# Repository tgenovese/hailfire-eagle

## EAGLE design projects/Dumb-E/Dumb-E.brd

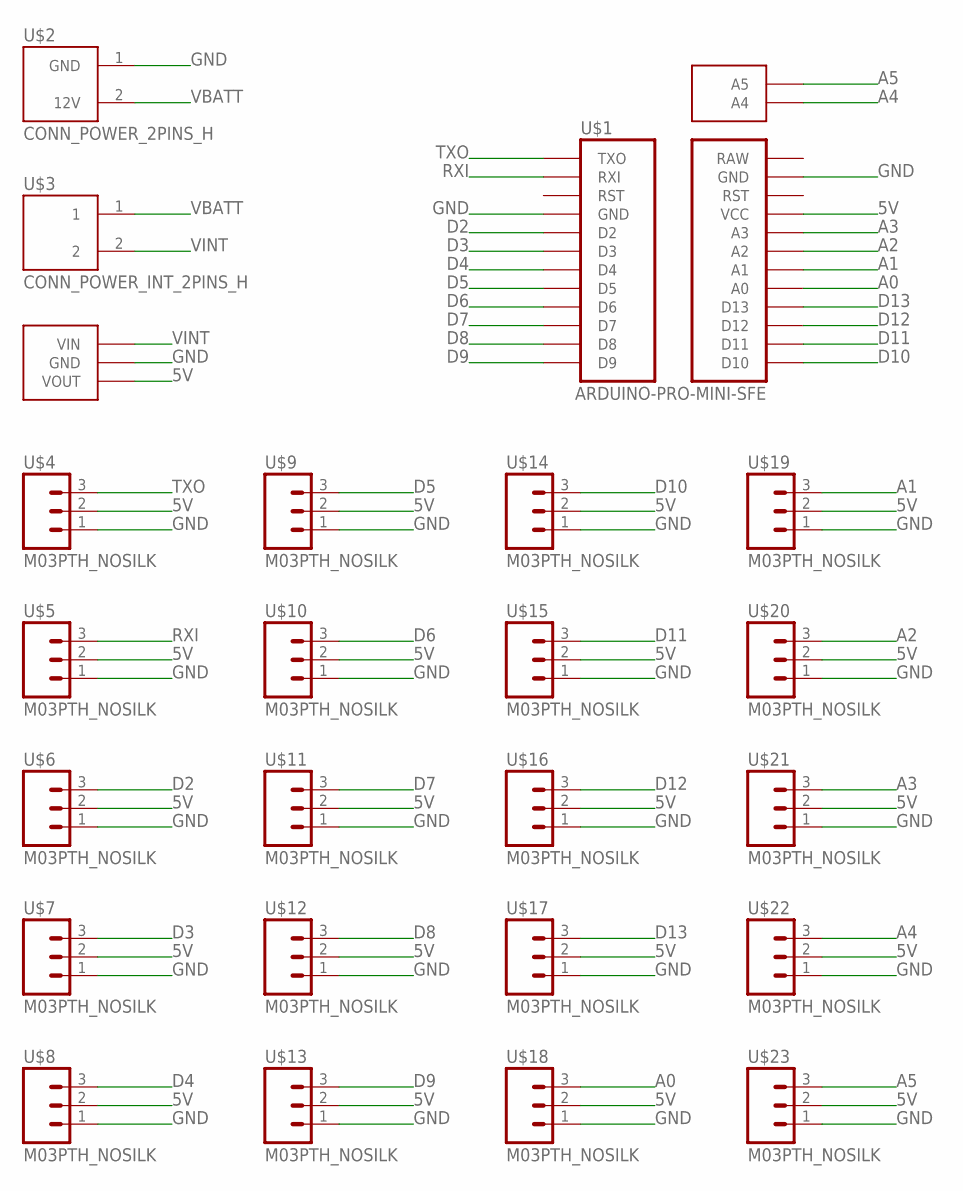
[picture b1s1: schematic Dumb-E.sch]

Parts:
U$1: ARDUINO-PRO-MINI-SFE; ARDUINO-PRO-MINI
U$2: CONN_POWER_2PINS_H; 2PINS_5MM_90DEG
U$3: CONN_POWER_INT_2PINS_H; 2PINS_5MM_90DEG
U$4, U$5, U$6, U$7, U$8, U$9, U$10, U$11, U$12, U$13, U$14, U$15, U$16, U$17, U$18, U$19, U$20, U$21, U$22, U$23: M03PTH_NOSILK; 1X03/NOSILK
U$25: DE-SW0XX

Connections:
5V: U$1.P$17 (VCC), U$4.2, U$5.2, U$6.2, U$7.2, U$8.2, U$9.2, U$10.2, U$11.2, U$12.2, U$13.2, U$14.2, U$15.2, U$16.2, U$17.2, U$18.2, U$19.2, U$20.2, U$21.2, U$22.2, U$23.2, U$25.VOUT
A0: U$1.P$9 (A0), U$18.3
A1: U$1.P$11 (A1), U$19.3
A2: U$1.P$13 (A2), U$20.3
A3: U$1.P$15 (A3), U$21.3
A4: U$1.P$26 (A4), U$22.3
A5: U$1.P$25 (A5), U$23.3
D2: U$1.P$16 (D2), U$6.3
D3: U$1.P$14 (D3), U$7.3
D4: U$1.P$12 (D4), U$8.3
D5: U$1.P$10 (D5), U$9.3
D6: U$1.P$8 (D6), U$10.3
D7: U$1.P$6 (D7), U$11.3
D8: U$1.P$4 (D8), U$12.3
D9: U$1.P$2 (D9), U$13.3
D10: U$1.P$1 (D10), U$14.3
D11: U$1.P$3 (D11), U$15.3
D12: U$1.P$5 (D12), U$16.3
D13: U$1.P$7 (D13), U$17.3
GND: U$1.P$18 (GND), U$1.P$21 (GND), U$2.1 (GND), U$4.1, U$5.1, U$6.1, U$7.1, U$8.1, U$9.1, U$10.1, U$11.1, U$12.1, U$13.1, U$14.1, U$15.1, U$16.1, U$17.1, U$18.1, U$19.1, U$20.1, U$21.1, U$22.1, U$23.1, U$25.GND
RXI: U$1.P$22 (RXI), U$5.3
TXO: U$1.P$24 (TXO), U$4.3
VBATT: U$2.2 (12V), U$3.1
VINT: U$3.2, U$25.VIN

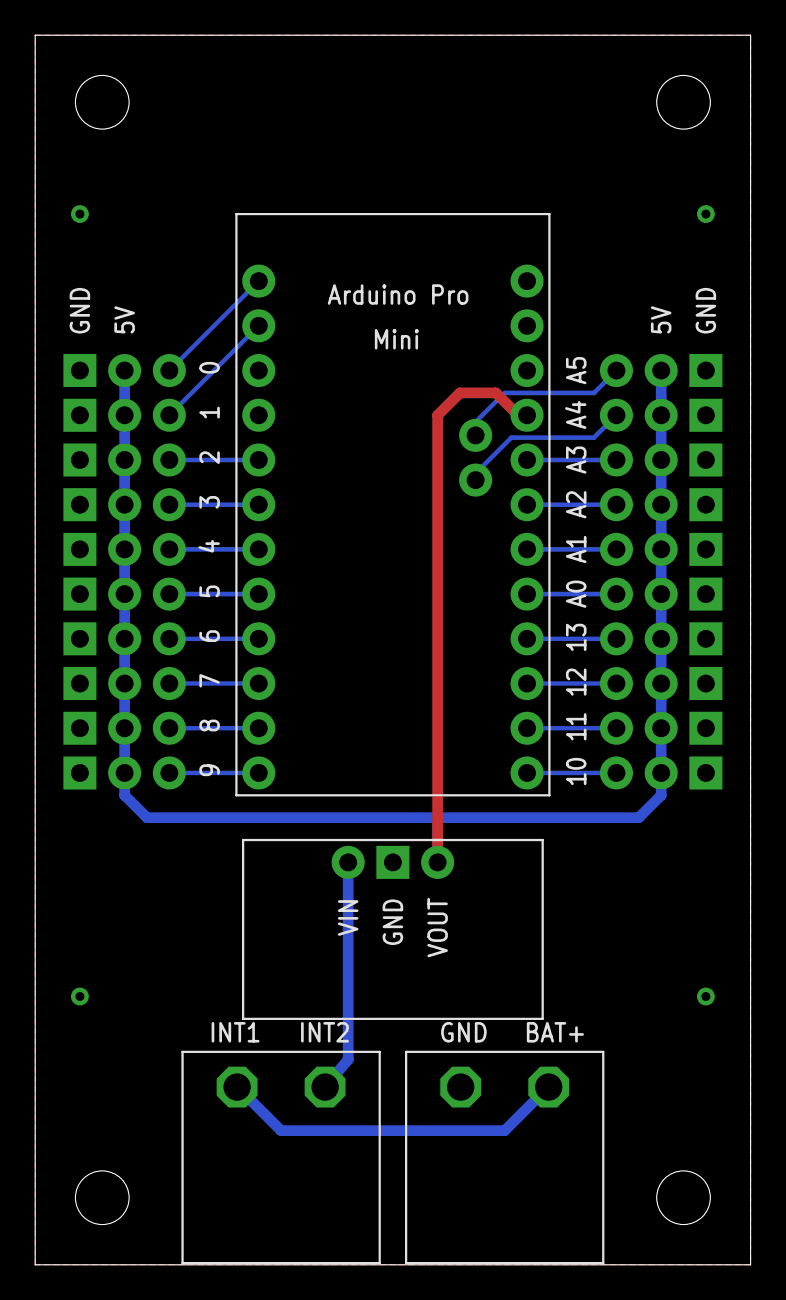
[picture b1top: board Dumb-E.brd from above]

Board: 2 copper layers, 40.6 x 69.8 mm, 24 parts (0 on the bottom side), 24 nets.

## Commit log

2016-03-28 Add EAGLE file hierarchy.
    Add SparkFun's scripts and library.
    To use the files in this directory:
    - open the EAGLE Control Panel,
    - open the Options/Directories... settings,
    - add each directory before the EAGLE-provided one (the separator is: ':')
2016-03-28 Add the SandwichBoard EAGLE project. This board connects the Summit/Overo stack to the Quicgate FPGA via an SPI interface. It also breakouts serial ports, I2C, PWM and ADC pins from the Overo. The di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
2016-03-28 Add the AlimBoard EAGLE project. This board carries the TRACO DC/DC converter and provides 3.3V and 5V to the robot's systems.
2016-03-28 Changed SparkFun's design rules file's description, in order to differenciate it from EAGLE's stock one.
2016-03-28 Add the CarrierBoard EAGLE project. This board carries and powers the FPGA/Gumstix stack and the extension cards.
2016-03-28 Add a personal library with the following symbols: - Carstac symbols: CARDSTAC_FULL_STD_ROWS_AB and CARDSTAC_FULL_STD_ROWS_GH - Gumstix symbols: SUMMIT_EXPANSION_CONN_SV1 - Power connectors symbols: 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
    The library also contains the following packages:
    - 2X32 (header, 0.1" spaced)
    - 2X20 (header, 0.1" spaced)
    - 2PINS_5MM_90DEG and 3PINS_3.81MM_90DEG (power connectors)
    The symbols and the packages are associated in devices for ready use in PCB projects.
2016-03-28 Modified the MAX33* parts to make them smaller, and modified the MAX3373E symbol to make it look more like the MAX3378E-MAX3393E
2016-03-28 Add the schematic and the board in the CarrierBoard project. The board should be ok (everything is routed, the silkscreen is done, and the mounting holes are there).
2016-03-28 Add the schematic and the board in the AlimBoard project. The board should be ok (everything is routed, the silkscreen is done, and the mounting holes are there). The board features: - 2 2-pin batter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
2016-03-28 Corrected the CARDSTAC_FULL_STD_ROWS_GH device (wrong pin numbering).
2016-03-28 Changed the orientation of 90deg silkscreen so that it will be easier to know where pin 1 is once the header is soldered (always leftmost when looking at the header, and on the bottom row if there ar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
2016-03-28 Add the symbols, footprints and devices for 1x3, 1x4 and 2x5 headers in vertical or 90deg mounts.
2016-03-28 Add: - symbol, footprint and device for the TRACO TEN 40-1220 DC/DC converter - symbol and device for an interrupter connector (for the AlimBoard).
2016-03-28 Add 0805 SMD capacitor.
2016-03-28 Add the symbols, footprints and devices for the MAX3373E, MAX3378E, MAX3390E to MAX3393E low voltage level translators.
2016-03-28 Add the footprint, symbol and device for the Gumstix Overo COMs. Those were extracted from the Summit schematic (PCB30001-R2185).
2016-03-28 Add the ADC33 Eagle project. This is an ADC board for the robot, carrying an MCP3008. The board is 2"x3" and should be complete.
2016-03-28 Add the schematic and the board in the SandwichBoard project. The board should be ok (everything is routed, the silkscreen is done, and the mounting holes are there).
2016-03-28 Add a script to generate a library from an EAGLE project. Can be used for example to reuse parts from Gumstix's designs.
2016-03-28 Add Microchip's MCP3008 A/D converter, shrouded 2x05 connectors (horizontal and right-angled) and TI's REF2933 3.3V voltage reference.
2016-03-28 Various modifications: - changed the 2X20 header to include the Summit expansion board outline, renamed the symbol, package and device to GUMSTIX_SUMMIT_SV1 - added a jumper symbol and solder jumper 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
2016-03-28 New EAGLE project: QuicOvero. This board serves the same purpose than the SandwichBoard, but without the Summit expansion board. The Gumstix Overo is directly connected on the QuicOvero, which itself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
2016-03-28 Modified the Gumstix Overo footprint because of BatchPCB's 8mil limit.
2016-03-28 Some adjustements: * CarrierBoard is now 3.4"x3" * AlimBoard, PWM50 and ADC33 are now 3.4"x2.1" * Moved the power connectors to the right of the AlimBoard, PWM50 and ADC33, away from the logic connec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
2016-03-28 Add TRACO TEN 15-2410WI (3.3V) and TEN 20-2411WIN (5V).
2016-03-28 Add HCPL-0630 and 0805 resistor parts.
2016-03-28 Add parts lists.
2016-03-28 Minor fixes in ADC33 and PWM50 boards.
2016-03-28 Put power traces on the bottom layer (soldering side).
2016-03-28 Add the PWM50 Eagle project. This is a PWM board for the robot, carrying four HCPL-0630. The board is 2"x3" and should be complete.
2016-03-28 Small fixes to AlimBoard.
2016-03-28 Add QuadEnc50 board, designed to provide logic level conversion from 5.0V to 3.3V to interface 4 quadrature encoders using 5.0V logic level to an FPGA using 3.3V IO.
2016-03-28 Add 5-pin 0.1" header
2016-03-28 Add CoreExpansion board (WIP). This board plugs in one of the expansion connectors of the CarrierBoard and hosts connectors for cards and devices common to every robot (motor controller, quadrature e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
2016-03-28 Progress on CoreExpansion board (should be finished). The level shifters for quadrature encoders were moved to another board.
2016-03-28 Update project files with the valid library paths.
2016-03-28 Update SparkFun library.
2016-03-28 Add gerber files archives sent for manufacturing to BatchPCB
2016-03-28 Add projects for smaller and simpler main stack (Gumstix Overo COM + Gumstix Pinto Expansion Board + QuicGate FPGA).
2016-03-28 Add M12, an 1x12 0.1" header
2016-03-28 Copy CoreExpansion schematics for the StackOverflow board.
2016-03-28 StackUnderflow WiP
2016-03-28 Add M04X2
2016-03-28 StackOverflow WiP
2016-03-28 Copy SandwichBoard schematics for the StackUnderflow board.
2016-03-28 Add Gumstix Pinto footprint. To be checked against Gumstix's schematic when Pinto is released.
2016-03-28 Update description
2016-03-28 Correct Gumstix Pinto dimensions and orientation.
2016-03-28 Add a switch to enable/disable spi level converter three-state output.
2016-03-28 Import the Pinto-TH expansion board schematics for reference.
    Those schematics originate at pubs.gumstix.com and are made available by Gumstix, Inc under a Creative Commons Attribution-ShareAlike2.5 License.
2016-03-28 Move some projects to the Attic: * CarrierBoard: provided power to the FPGA/Gumstix stack and carried 2*64pin expansion connectors * SandwichBoard: plugged on top of the FPGA and provided a connector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
    Those projects are replaced by:
    * CarrierBoard and SandwichBoard/QuicOvero replaced by StackUnderflow (which carries the FPGA and a Pinto/Overo stack)
    * CoreExpansion: replaced by StackOverflow (which plugs on top of the FPGA and carries 14 HE10
2016-03-28 Add descriptions for projects folders
2016-03-28 Add a 40-pin version of the Gumstix Pinto (without the extra GPIOs and MMC signals), easier to place on a board.
2016-03-28 Rename Gumstix Pinto symbol, footprint and device to GUMSTIX_PINTO_60PIN
2016-03-28 Modify the StackUnderflow board to take into account the corrected Gumstix Pinto (WiP)[C
2016-03-28 StackOverflow: change some of the layout
2016-03-28 Finish StackOverflow board.
2016-03-28 Changes on StackOverflow: * Swap ADCX_CS and ADCX_MOSI pins so as to have the CS signal on the pin affected by the pullup present on the Quicgate board. * Connect unused pins on ADC connectors and GP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
2016-03-28 Finish StackUnderflow board.
2016-03-28 Modify StackOverflow to de-specialized most connectors. The board now provides: * 7 8-lines expansion connectors, * 1 ADC33 connector, * 1 PWM50 connector, * 1 QuadEnc connector, * 4 motor controller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
2016-03-28 Add FPGA pin assignment list to match Quicgate pins with FPGA pins and MainStack pins.
2016-03-28 Changes on StackOverflow: * renamed EXTXX signals to EXT[1:4]_[0:7] signals. * removed a current loop on 3.3V power line
2016-03-28 Set version on silkscreens. Add Gerber files for boards submitted to BatchPCB DRC bot. Del executable property on parts lists.
2016-03-28 Fix Arduino-Pro-Mini part.
2016-03-28 Add EAGLE projects for two related boards: * JoystickBreakout: breaks out the two axis and the select line of the SparkFun thumb joystick * ThumbLCDBase: supports a serial-enabled SparkFun LCD, a Joy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
2016-03-28 Set version on silkscreens. Add Gerber files for boards submitted to BatchPCB DRC bot.
2016-03-28 Change drills to 2mm. Connect LCD to digital pin 4 instead of hardware TX to program the Arduino in situ.
2016-03-28 Add Arduino Pro Mini outline.
2016-03-28 Change QuadEnc50 board to add pull-ups for channels A, B and index. Change encoder connectors to match HEDS5540 pinout.
2016-03-28 Add the EAGLE project for the robot's RoboClaw Add-on board. This board converts the UART and encoders 0.1" headers to separate connector sockets.
2016-03-28 Add Gerber files for board submitted to BatchPCB DRC bot.
2016-03-28 Add EAGLE files for Dumb-E baseboard for Arduino Pro Mini. Dumb-E.brd uploaded to board house oshpark.com.
2016-03-28 Add silkscreen-less M03, M04 and M05 variants.
2016-03-28 Fix pin layout of encoder connectors.
